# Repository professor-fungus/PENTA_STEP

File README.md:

# PENTA_STEP

I hate tracking down EMI through jumpers.

This is my attempt to create a stepper driver board that can be loaded with up to 5 stepper drives.

If one fails, it will require soldering rework; this may not be optimal for those without SMD rework tools.

The drives utilize Trinamic TMC5160's, based on the schematic for the TMC5160-BOB.

Why five drives? 
* 3 axes and 2 extruders for 3D printing.
* 3 cartesian axes and 2 orthogonal axes for milling.
* 5 axis robots.
* Too little space for 4 drives on a 100mmx100mm board from JLCPCB, so go big or go home.

If less than 5 axes are desired, less can be populated (although this wouldn't save much).

Target is a 4-layer board currently.

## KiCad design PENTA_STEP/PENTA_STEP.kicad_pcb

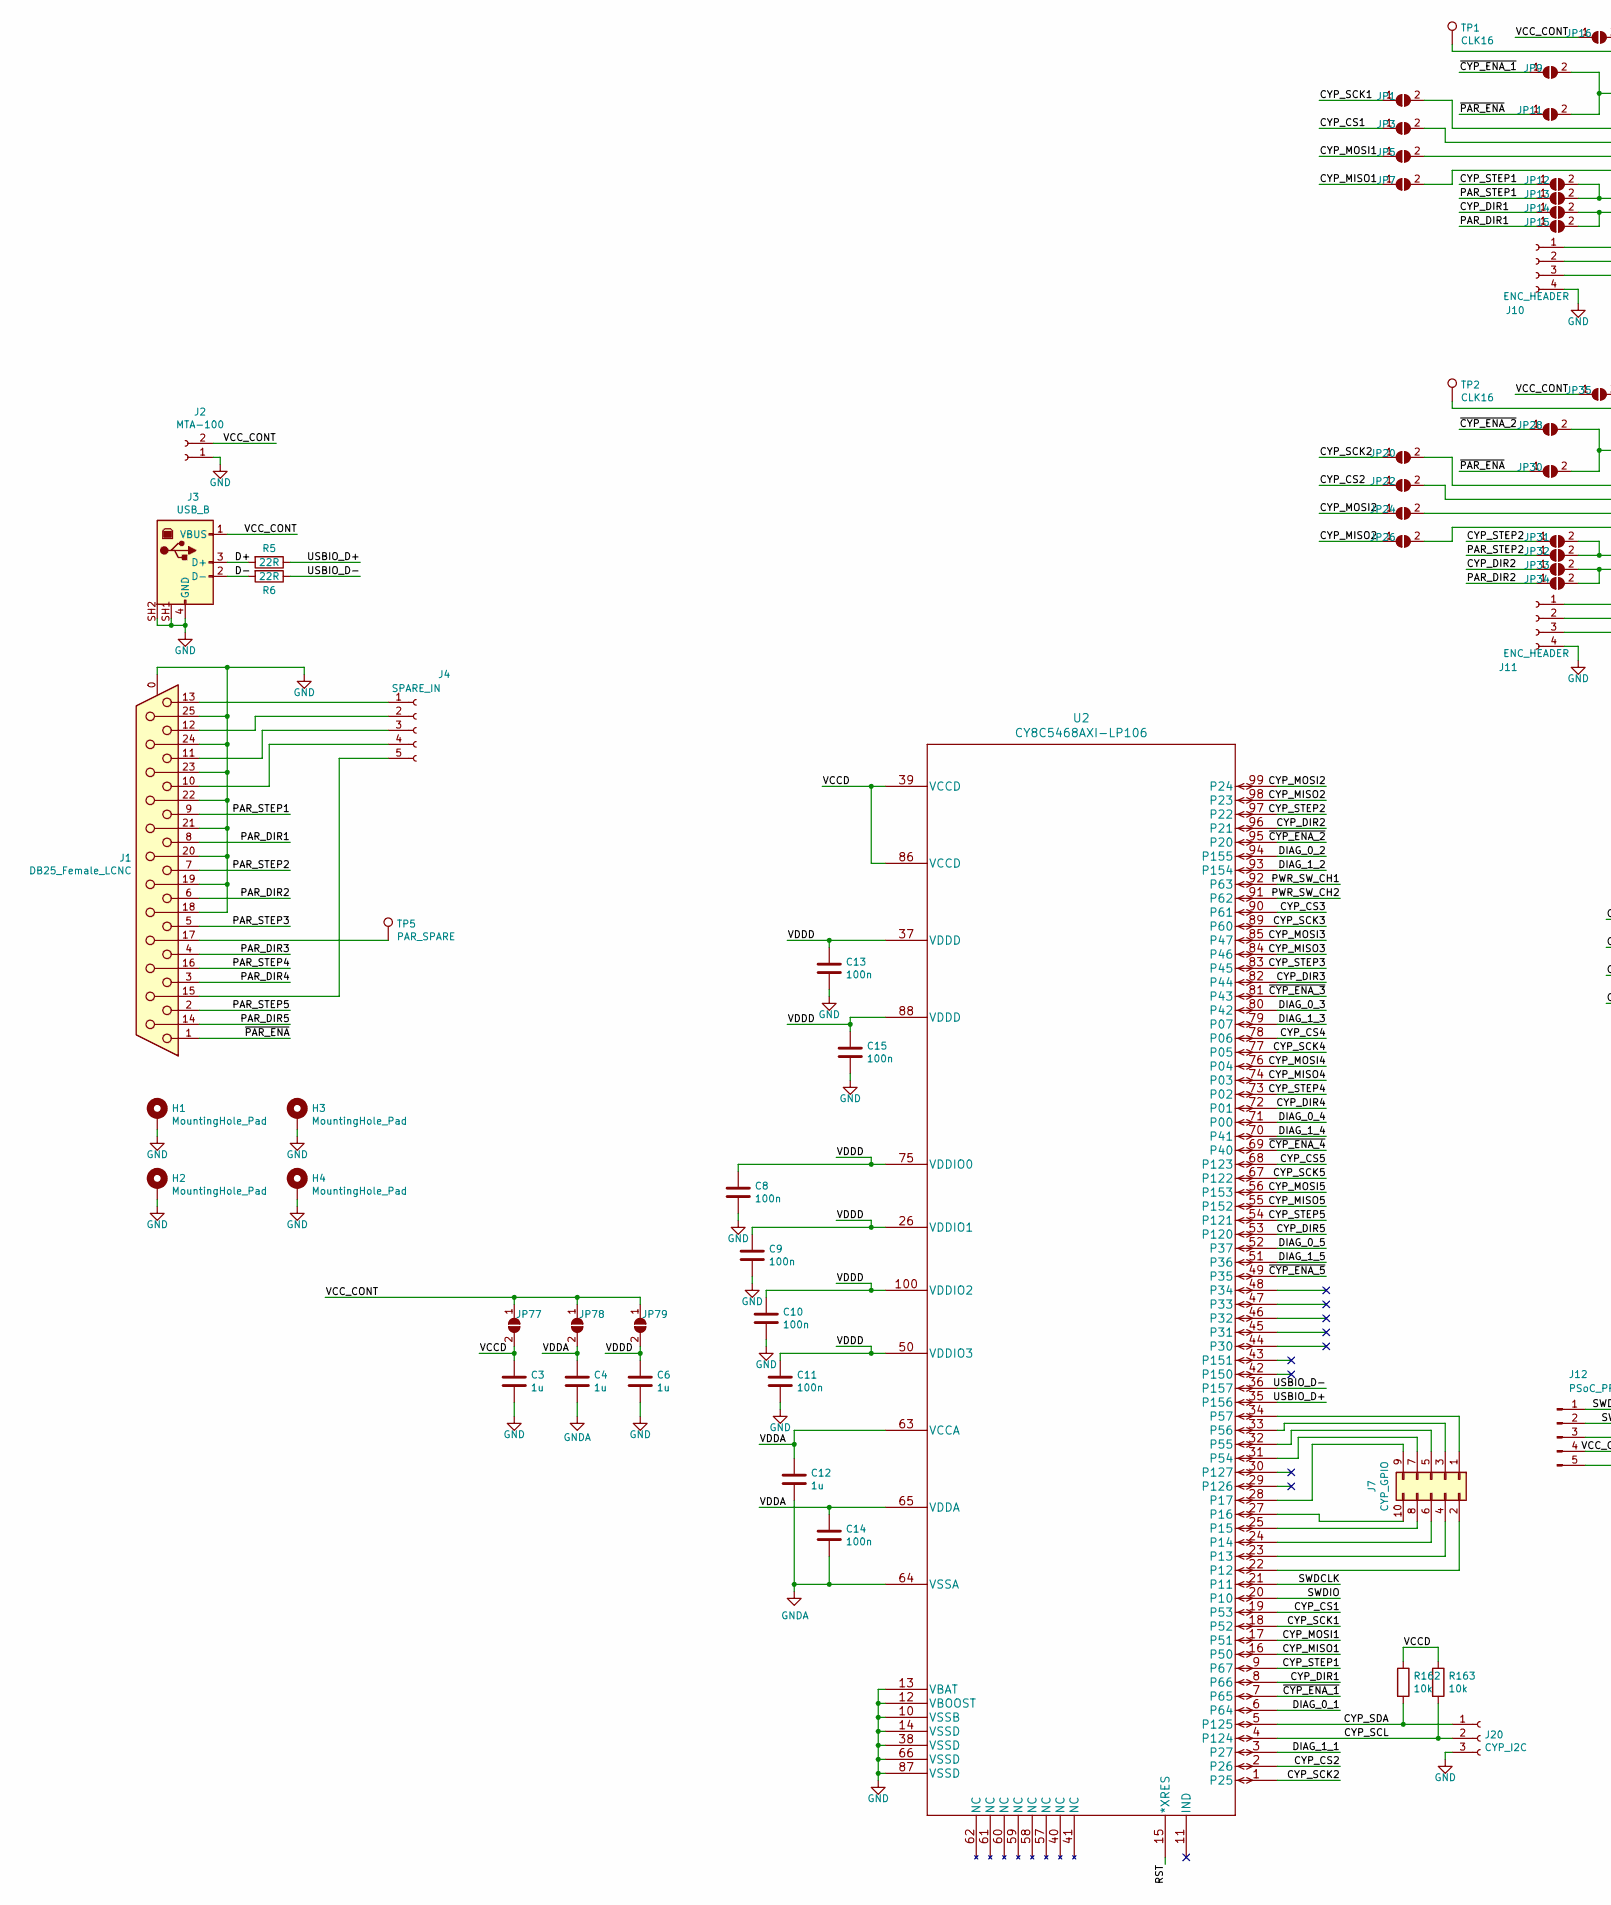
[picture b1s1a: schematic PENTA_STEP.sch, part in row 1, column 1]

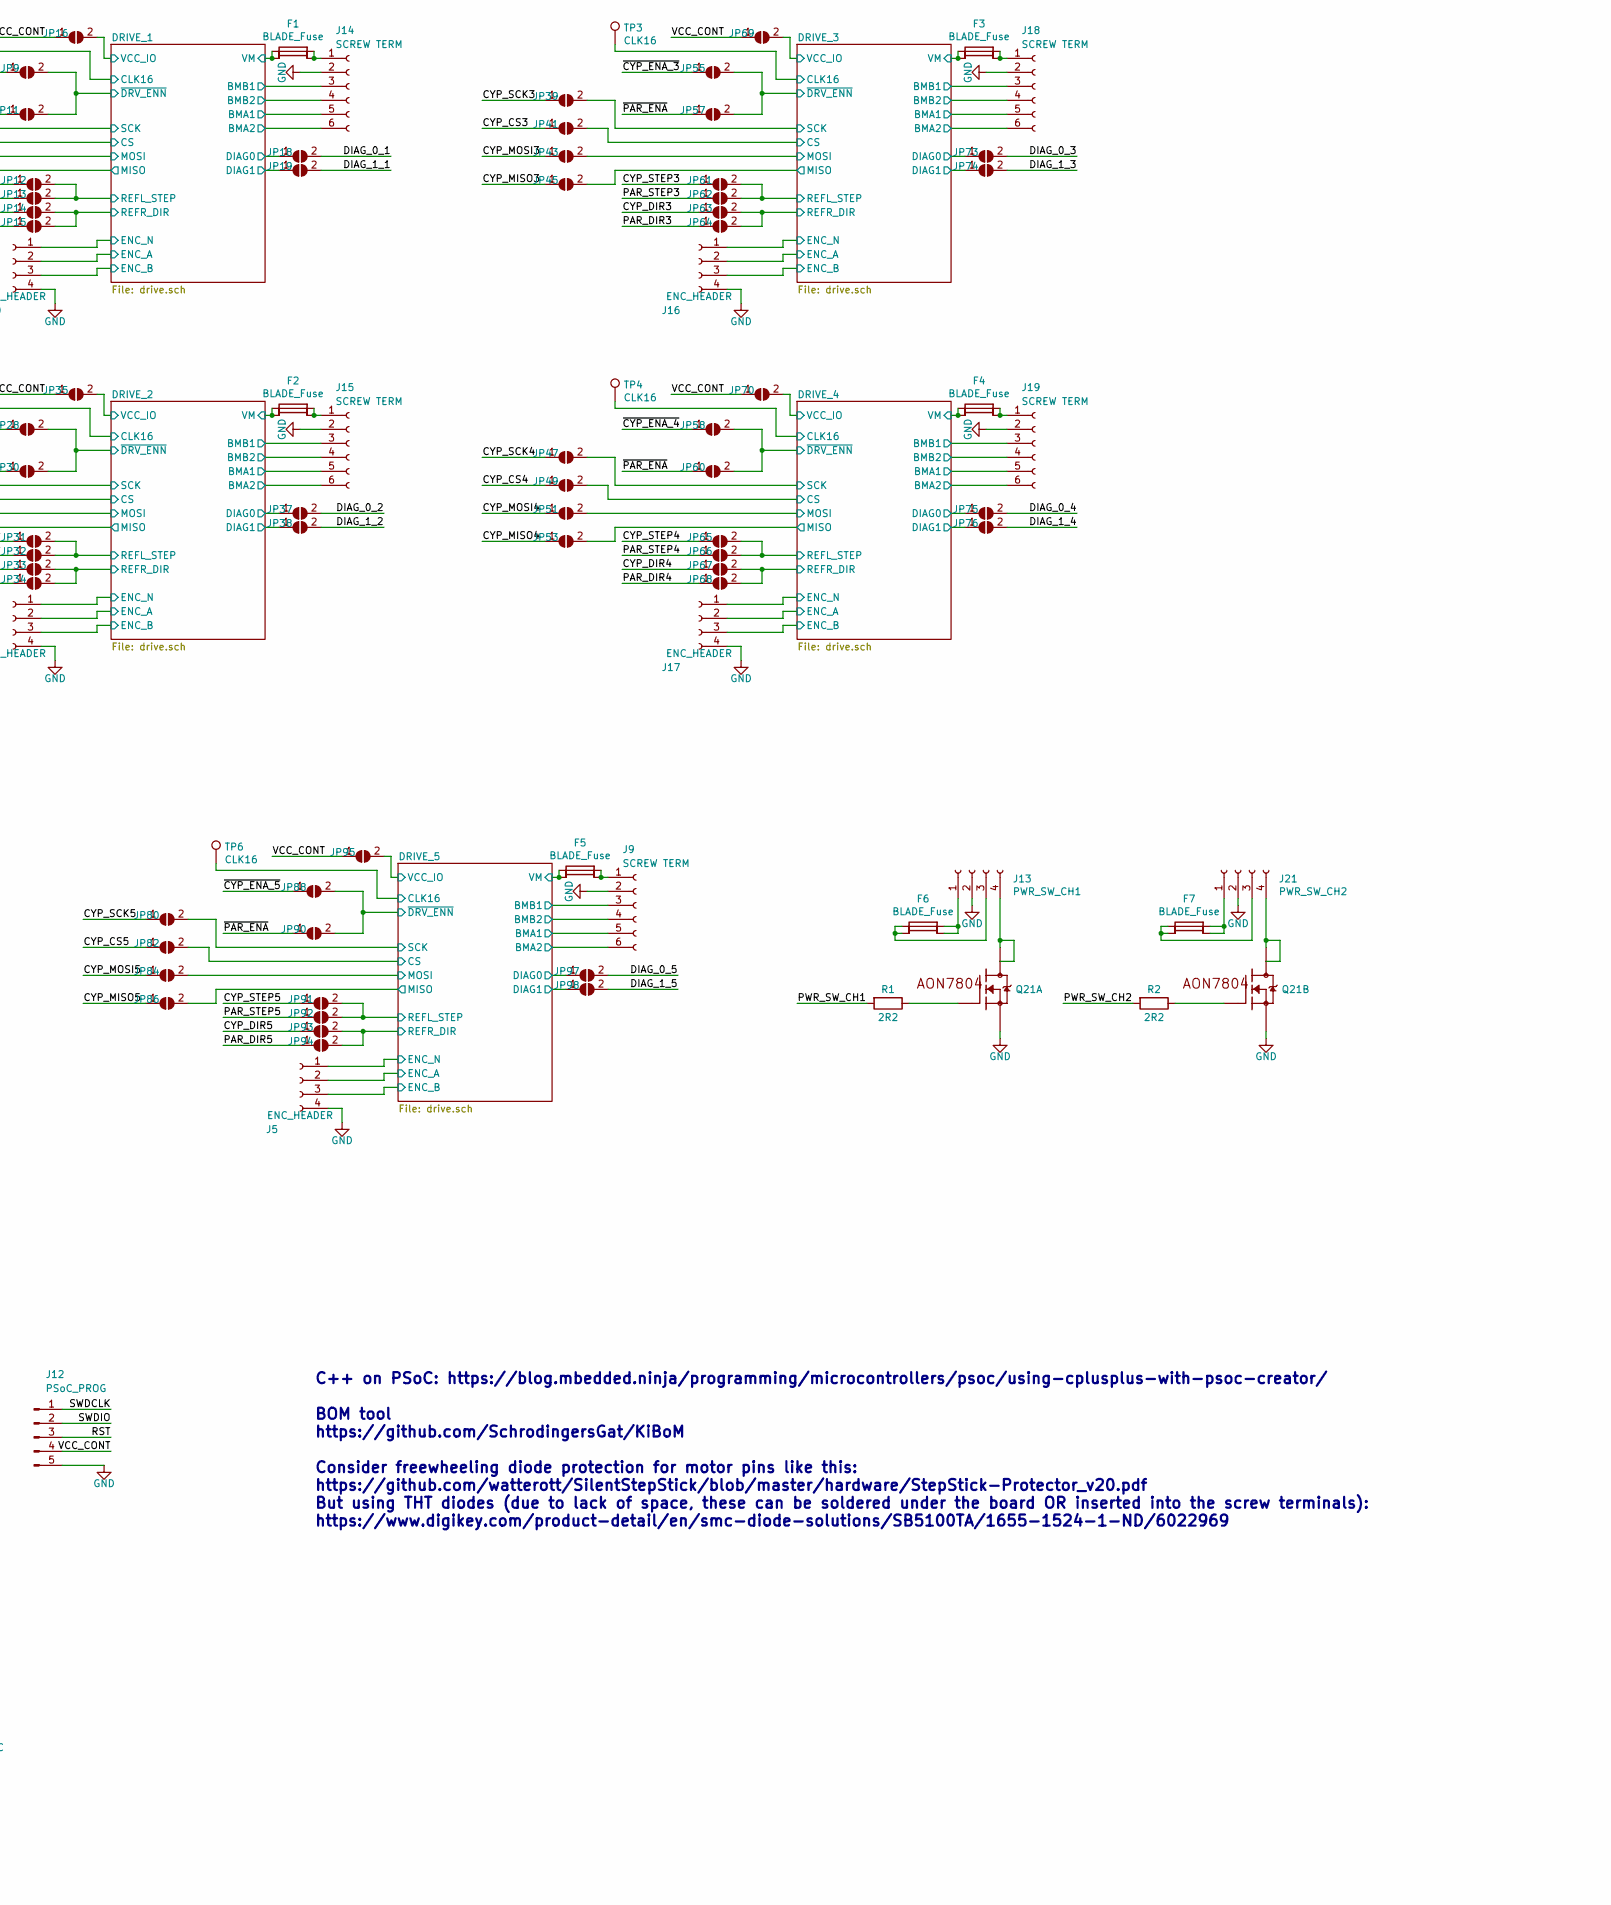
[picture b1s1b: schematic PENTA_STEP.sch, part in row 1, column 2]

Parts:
C3, C4, C6, C12: 1u; C_0603_1608Metric_Pad1.05x0.95mm_HandSolder; MPN CL10B105MO8NNWC
C8, C9, C10, C11, C13, C14, C15: 100n; C_0603_1608Metric_Pad1.05x0.95mm_HandSolder; MPN 06031C104KAT2A
F1, F2, F3, F4, F5: BLADE_Fuse; keystone_3549_2_fuseholder_THT; MPN 3549-2
F6, F7: BLADE_Fuse; keystone_3568_10_fuseholder_THT; MPN 3568-10
H1, H2, H3, H4: MountingHole_Pad; MountingHole_4.5mm_Pad_Via
J1: DB25_Female_LCNC; DSUB-25_Female_Horizontal_P2.77x2.84mm_EdgePinOffset7.70mm_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; MPN DB25-SL-25
J2: MTA-100; 640456-2; MPN 640456-2
J3: USB_B; CUI_UJ2-BH-W1-TH; MPN UJ2-BH-W1-TH
J4: SPARE_IN; PinHeader_1x05_P2.54mm_Vertical
J5, J10, J11, J16, J17: ENC_HEADER; PinHeader_1x04_P1.00mm_Vertical; MPN HDR100MET40M-G-RA-TH
J7: CYP_GPIO; PinHeader_2x05_P2.54mm_Vertical
J9, J14, J15, J18, J19: SCREW TERM; CUI_TB002-500-06BE; MPN TB002-500-06BE
J12: PSoC_PROG; PinHeader_1x05_P2.54mm_Vertical
J13: PWR_SW_CH1; 1776275-4; MPN 1988972
J20: CYP_I2C; PinHeader_1x03_P2.54mm_Vertical
J21: PWR_SW_CH2; 1776275-4; MPN 1988972
JP1, JP3, JP5, JP7, JP9, JP11, JP12, JP13, JP14, JP15, JP16, JP18, JP19, JP20, JP22, JP24, JP26, JP28, JP30, JP31, JP32, JP33, JP34, JP35, JP37, JP38, JP39, JP41, JP43, JP45, JP47, JP49, JP51, JP53, JP55, JP57, JP58, JP60, JP61, JP62, JP63, JP64, JP65, JP66, JP67, JP68, JP69, JP70, JP73, JP74, JP75, JP76, JP77, JP78, JP79, JP80, JP82, JP84, JP86, JP88, JP90, JP91, JP92, JP93, JP94, JP95, JP97, JP98: SolderJumper_2_Open; small_triangle_jumper
Q21: AON7804; DFN3X3_AON7804; MPN AON7804
R1, R2: 2R2; R_0603_1608Metric_Pad1.05x0.95mm_HandSolder; MPN RC0603FR-072R2L
R5, R6: 22R; R_0603_1608Metric_Pad1.05x0.95mm_HandSolder; MPN ERJ-3EKF22R0V
R162, R163: 10k; R_0603_1608Metric_Pad1.05x0.95mm_HandSolder; MPN RC0603JR-0710KL
TP1, TP2, TP3, TP4, TP6: CLK16; TestPoint_Pad_D1.0mm
TP5: PAR_SPARE; TestPoint_Pad_D1.0mm
U2: CY8C5468AXI-LP106; MPN CY8C5468AXI-LP106

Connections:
/CYP_CS1: JP3.1 (A), U2.19 (P53)
/CYP_CS2: JP22.1 (A), U2.2 (P26)
/CYP_CS3: JP41.1 (A), U2.90 (P61)
/CYP_CS4: JP49.1 (A), U2.78 (P06)
/CYP_CS5: JP82.1 (A), U2.68 (P123)
/CYP_DIR1: JP14.1 (A), U2.8 (P66)
/CYP_DIR2: JP33.1 (A), U2.96 (P21)
/CYP_DIR3: JP63.1 (A), U2.82 (P44)
/CYP_DIR4: JP67.1 (A), U2.72 (P01)
/CYP_DIR5: JP93.1 (A), U2.53 (P120)
/CYP_MISO1: JP7.1 (A), U2.16 (P50)
/CYP_MISO2: JP26.1 (A), U2.98 (P23)
/CYP_MISO3: JP45.1 (A), U2.84 (P46)
/CYP_MISO4: JP53.1 (A), U2.74 (P03)
/CYP_MISO5: JP86.1 (A), U2.55 (P152)
/CYP_MOSI1: JP5.1 (A), U2.17 (P51)
/CYP_MOSI2: JP24.1 (A), U2.99 (P24)
/CYP_MOSI3: JP43.1 (A), U2.85 (P47)
/CYP_MOSI4: JP51.1 (A), U2.76 (P04)
/CYP_MOSI5: JP84.1 (A), U2.56 (P153)
/CYP_SCK1: JP1.1 (A), U2.18 (P52)
/CYP_SCK2: JP20.1 (A), U2.1 (P25)
/CYP_SCK3: JP39.1 (A), U2.89 (P60)
/CYP_SCK4: JP47.1 (A), U2.77 (P05)
/CYP_SCK5: JP80.1 (A), U2.67 (P122)
/CYP_SCL: J20.2, R163.2, U2.4 (P124)
/CYP_SDA: J20.1, R162.2, U2.5 (P125)
/CYP_STEP1: JP12.1 (A), U2.9 (P67)
/CYP_STEP2: JP31.1 (A), U2.97 (P22)
/CYP_STEP3: JP61.1 (A), U2.83 (P45)
/CYP_STEP4: JP65.1 (A), U2.73 (P02)
/CYP_STEP5: JP91.1 (A), U2.54 (P121)
/D+: J3.3 (D+), R5.2
/D-: J3.2 (D-), R6.2
/DIAG_0_1: JP18.2 (B), U2.6 (P64)
/DIAG_0_2: JP37.2 (B), U2.94 (P155)
/DIAG_0_3: JP73.2 (B), U2.80 (P42)
/DIAG_0_4: JP75.2 (B), U2.71 (P00)
/DIAG_0_5: JP97.2 (B), U2.52 (P37)
/DIAG_1_1: JP19.2 (B), U2.3 (P27)
/DIAG_1_2: JP38.2 (B), U2.93 (P154)
/DIAG_1_3: JP74.2 (B), U2.79 (P07)
/DIAG_1_4: JP76.2 (B), U2.70 (P41)
/DIAG_1_5: JP98.2 (B), U2.51 (P36)
/DRIVE_1/BMA1: J14.5; also elsewhere on the board
/DRIVE_1/BMA2: J14.6; also elsewhere on the board
/DRIVE_1/BMB1: J14.3; also elsewhere on the board
/DRIVE_1/BMB2: J14.4; also elsewhere on the board
/DRIVE_1/CLK16: TP1.1; also elsewhere on the board
/DRIVE_1/CS: JP3.2 (B); also elsewhere on the board
/DRIVE_1/DIAG0: JP18.1 (A); also elsewhere on the board
/DRIVE_1/DIAG1: JP19.1 (A); also elsewhere on the board
/DRIVE_1/ENC_A: J10.2; also elsewhere on the board
/DRIVE_1/ENC_B: J10.3; also elsewhere on the board
/DRIVE_1/ENC_N: J10.1; also elsewhere on the board
/DRIVE_1/MISO: JP7.2 (B); also elsewhere on the board
/DRIVE_1/MOSI: JP5.2 (B); also elsewhere on the board
/DRIVE_1/REFL_STEP: JP12.2 (B), JP13.2 (B); also elsewhere on the board
/DRIVE_1/REFR_DIR: JP14.2 (B), JP15.2 (B); also elsewhere on the board
/DRIVE_1/SCK: JP1.2 (B); also elsewhere on the board
/DRIVE_1/VCC_IO: JP16.2 (B); also elsewhere on the board
/DRIVE_1/VM: F1.1, F1.2; also elsewhere on the board
/DRIVE_1/~DRV_ENN: JP9.2 (B), JP11.2 (B); also elsewhere on the board
/DRIVE_2/BMA1: J15.5; also elsewhere on the board
/DRIVE_2/BMA2: J15.6; also elsewhere on the board
/DRIVE_2/BMB1: J15.3; also elsewhere on the board
/DRIVE_2/BMB2: J15.4; also elsewhere on the board
/DRIVE_2/CLK16: TP2.1; also elsewhere on the board
/DRIVE_2/CS: JP22.2 (B); also elsewhere on the board
/DRIVE_2/DIAG0: JP37.1 (A); also elsewhere on the board
/DRIVE_2/DIAG1: JP38.1 (A); also elsewhere on the board
/DRIVE_2/ENC_A: J11.2; also elsewhere on the board
/DRIVE_2/ENC_B: J11.3; also elsewhere on the board
/DRIVE_2/ENC_N: J11.1; also elsewhere on the board
/DRIVE_2/MISO: JP26.2 (B); also elsewhere on the board
/DRIVE_2/MOSI: JP24.2 (B); also elsewhere on the board
/DRIVE_2/REFL_STEP: JP31.2 (B), JP32.2 (B); also elsewhere on the board
/DRIVE_2/REFR_DIR: JP33.2 (B), JP34.2 (B); also elsewhere on the board
/DRIVE_2/SCK: JP20.2 (B); also elsewhere on the board
/DRIVE_2/VCC_IO: JP35.2 (B); also elsewhere on the board
/DRIVE_2/VM: F2.1, F2.2; also elsewhere on the board
/DRIVE_2/~DRV_ENN: JP28.2 (B), JP30.2 (B); also elsewhere on the board
/DRIVE_3/BMA1: J18.5; also elsewhere on the board
/DRIVE_3/BMA2: J18.6; also elsewhere on the board
/DRIVE_3/BMB1: J18.3; also elsewhere on the board
/DRIVE_3/BMB2: J18.4; also elsewhere on the board
/DRIVE_3/CLK16: TP3.1; also elsewhere on the board
/DRIVE_3/CS: JP41.2 (B); also elsewhere on the board
/DRIVE_3/DIAG0: JP73.1 (A); also elsewhere on the board
/DRIVE_3/DIAG1: JP74.1 (A); also elsewhere on the board
/DRIVE_3/ENC_A: J16.2; also elsewhere on the board
/DRIVE_3/ENC_B: J16.3; also elsewhere on the board
/DRIVE_3/ENC_N: J16.1; also elsewhere on the board
/DRIVE_3/MISO: JP45.2 (B); also elsewhere on the board
/DRIVE_3/MOSI: JP43.2 (B); also elsewhere on the board
/DRIVE_3/REFL_STEP: JP61.2 (B), JP62.2 (B); also elsewhere on the board
/DRIVE_3/REFR_DIR: JP63.2 (B), JP64.2 (B); also elsewhere on the board
/DRIVE_3/SCK: JP39.2 (B); also elsewhere on the board
/DRIVE_3/VCC_IO: JP69.2 (B); also elsewhere on the board
/DRIVE_3/VM: F3.1, F3.2; also elsewhere on the board
/DRIVE_3/~DRV_ENN: JP55.2 (B), JP57.2 (B); also elsewhere on the board
/DRIVE_4/BMA1: J19.5; also elsewhere on the board
/DRIVE_4/BMA2: J19.6; also elsewhere on the board
/DRIVE_4/BMB1: J19.3; also elsewhere on the board
/DRIVE_4/BMB2: J19.4; also elsewhere on the board
/DRIVE_4/CLK16: TP4.1; also elsewhere on the board
/DRIVE_4/CS: JP49.2 (B); also elsewhere on the board
/DRIVE_4/DIAG0: JP75.1 (A); also elsewhere on the board
/DRIVE_4/DIAG1: JP76.1 (A); also elsewhere on the board
/DRIVE_4/ENC_A: J17.2; also elsewhere on the board
/DRIVE_4/ENC_B: J17.3; also elsewhere on the board
/DRIVE_4/ENC_N: J17.1; also elsewhere on the board
/DRIVE_4/MISO: JP53.2 (B); also elsewhere on the board
/DRIVE_4/MOSI: JP51.2 (B); also elsewhere on the board
/DRIVE_4/REFL_STEP: JP65.2 (B), JP66.2 (B); also elsewhere on the board
/DRIVE_4/REFR_DIR: JP67.2 (B), JP68.2 (B); also elsewhere on the board
/DRIVE_4/SCK: JP47.2 (B); also elsewhere on the board
/DRIVE_4/VCC_IO: JP70.2 (B); also elsewhere on the board
/DRIVE_4/VM: F4.1, F4.2; also elsewhere on the board
/DRIVE_4/~DRV_ENN: JP58.2 (B), JP60.2 (B); also elsewhere on the board
/DRIVE_5/BMA1: J9.5; also elsewhere on the board
/DRIVE_5/BMA2: J9.6; also elsewhere on the board
/DRIVE_5/BMB1: J9.3; also elsewhere on the board
/DRIVE_5/BMB2: J9.4; also elsewhere on the board
/DRIVE_5/CLK16: TP6.1; also elsewhere on the board
/DRIVE_5/CS: JP82.2 (B); also elsewhere on the board
/DRIVE_5/DIAG0: JP97.1 (A); also elsewhere on the board
/DRIVE_5/DIAG1: JP98.1 (A); also elsewhere on the board
/DRIVE_5/ENC_A: J5.2; also elsewhere on the board
/DRIVE_5/ENC_B: J5.3; also elsewhere on the board
/DRIVE_5/ENC_N: J5.1; also elsewhere on the board
/DRIVE_5/MISO: JP86.2 (B); also elsewhere on the board
/DRIVE_5/MOSI: JP84.2 (B); also elsewhere on the board
/DRIVE_5/REFL_STEP: JP91.2 (B), JP92.2 (B); also elsewhere on the board
/DRIVE_5/REFR_DIR: JP93.2 (B), JP94.2 (B); also elsewhere on the board
/DRIVE_5/SCK: JP80.2 (B); also elsewhere on the board
/DRIVE_5/VCC_IO: JP95.2 (B); also elsewhere on the board
/DRIVE_5/VM: F5.1, F5.2; also elsewhere on the board
/DRIVE_5/~DRV_ENN: JP88.2 (B), JP90.2 (B); also elsewhere on the board
/PAR_DIR1: J1.8, JP15.1 (A)
/PAR_DIR2: J1.6, JP34.1 (A)
/PAR_DIR3: J1.4, JP64.1 (A)
/PAR_DIR4: J1.3, JP68.1 (A)
/PAR_DIR5: J1.14, JP94.1 (A)
/PAR_STEP1: J1.9, JP13.1 (A)
/PAR_STEP2: J1.7, JP32.1 (A)
/PAR_STEP3: J1.5, JP62.1 (A)
/PAR_STEP4: J1.16, JP66.1 (A)
/PAR_STEP5: J1.2, JP92.1 (A)
/PWR_SW_CH1: R1.2, U2.92 (P63)
/PWR_SW_CH2: R2.2, U2.91 (P62)
/RST: J12.3, U2.15 (*XRES)
/SWDCLK: J12.1, U2.21 (P11)
/SWDIO: J12.2, U2.20 (P10)
/USBIO_D+: R5.1, U2.35 (P156)
/USBIO_D-: R6.1, U2.36 (P157)
/VCCD: C3.1, JP77.2 (B), R162.1, R163.1, U2.39 (VCCD), U2.86 (VCCD)
/VCC_CONT: J2.2, J3.1 (VBUS), J12.4, JP16.1 (A), JP35.1 (A), JP69.1 (A), JP70.1 (A), JP77.1 (A), JP78.1 (A), JP79.1 (A), JP95.1 (A)
/VDDA: C4.1, C12.1, C14.1, JP78.2 (B), U2.63 (VCCA), U2.65 (VDDA)
/VDDD: C6.1, C8.1, C9.1, C10.1, C11.1, C13.1, C15.1, JP79.2 (B), U2.26 (VDDIO1), U2.37 (VDDD), U2.50 (VDDIO3), U2.75 (VDDIO0), U2.88 (VDDD), U2.100 (VDDIO2)
/~CYP_ENA_1: JP9.1 (A), U2.7 (P65)
/~CYP_ENA_2: JP28.1 (A), U2.95 (P20)
/~CYP_ENA_3: JP55.1 (A), U2.81 (P43)
/~CYP_ENA_4: JP58.1 (A), U2.69 (P40)
/~CYP_ENA_5: JP88.1 (A), U2.49 (P35)
/~PAR_ENA: J1.1, JP11.1 (A), JP30.1 (A), JP57.1 (A), JP60.1 (A), JP90.1 (A)
GND: C3.2, C6.2, C8.2, C9.2, C10.2, C11.2, C13.2, C15.2, H1.1, H2.1, H3.1, H4.1, J1.0 (PAD), J1.18, J1.19, J1.20, J1.21, J1.22, J1.23, J1.24, J1.25, J2.1, J3.4 (GND), J3.SH1, J3.SH2, J5.4, J9.2, J10.4, J11.4, J12.5, J13.2, J14.2, J15.2, J16.4, J17.4, J18.2, J19.2, J20.3, J21.2, Q21.S1 (S), Q21.S2 (S), U2.10 (VSSB), U2.12 (VBOOST), U2.13 (VBAT), U2.14 (VSSD), U2.38 (VSSD), U2.66 (VSSD), U2.87 (VSSD); also elsewhere on the board
GNDA: C4.2, C12.2, C14.2, U2.64 (VSSA)
unnamed: F1.3, F1.4, J14.1
unnamed: F2.3, F2.4, J15.1
unnamed: F3.3, F3.4, J18.1
unnamed: F4.3, F4.4, J19.1
unnamed: F5.3, F5.4, J9.1
unnamed: F6.1, F6.2, J13.3
unnamed: F6.3, F6.4, J13.1
unnamed: F7.1, F7.2, J21.3
unnamed: F7.3, F7.4, J21.1
unnamed: J1.10, J4.4
unnamed: J1.11, J4.3
unnamed: J1.12, J4.2
unnamed: J1.13, J4.1
unnamed: J1.15, J4.5
unnamed: J1.17, TP5.1
unnamed: J7.1, U2.34 (P57)
unnamed: J7.2, U2.22 (P12)
unnamed: J7.3, U2.33 (P56)
unnamed: J7.4, U2.23 (P13)
unnamed: J7.5, U2.32 (P55)
unnamed: J7.6, U2.24 (P14)
unnamed: J7.7, U2.31 (P54)
unnamed: J7.8, U2.25 (P15)
unnamed: J7.9, U2.28 (P17)
unnamed: J7.10, U2.27 (P16)
unnamed: J13.4, Q21.D1 (D), Q21.D1A (D1)
unnamed: J21.4, Q21.D2 (D), Q21.D2A (D1)
unnamed: Q21.G1 (G), R1.1
unnamed: Q21.G2 (G), R2.1

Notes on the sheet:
C++ on PSoC: https://blog.mbedded.ninja/programming/microcontrollers/psoc/using-cplusplus-with-psoc-creator/ BOM tool https://github.com/SchrodingersGat/KiBoM Consider freewheeling diode protection for motor pins like this: https://github.com/watterott/SilentStepStick/blob/master/hardware/StepStick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

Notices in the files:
parts and their libraries:
Copyright 2016 Accelerated Designs. All rights reserved.
